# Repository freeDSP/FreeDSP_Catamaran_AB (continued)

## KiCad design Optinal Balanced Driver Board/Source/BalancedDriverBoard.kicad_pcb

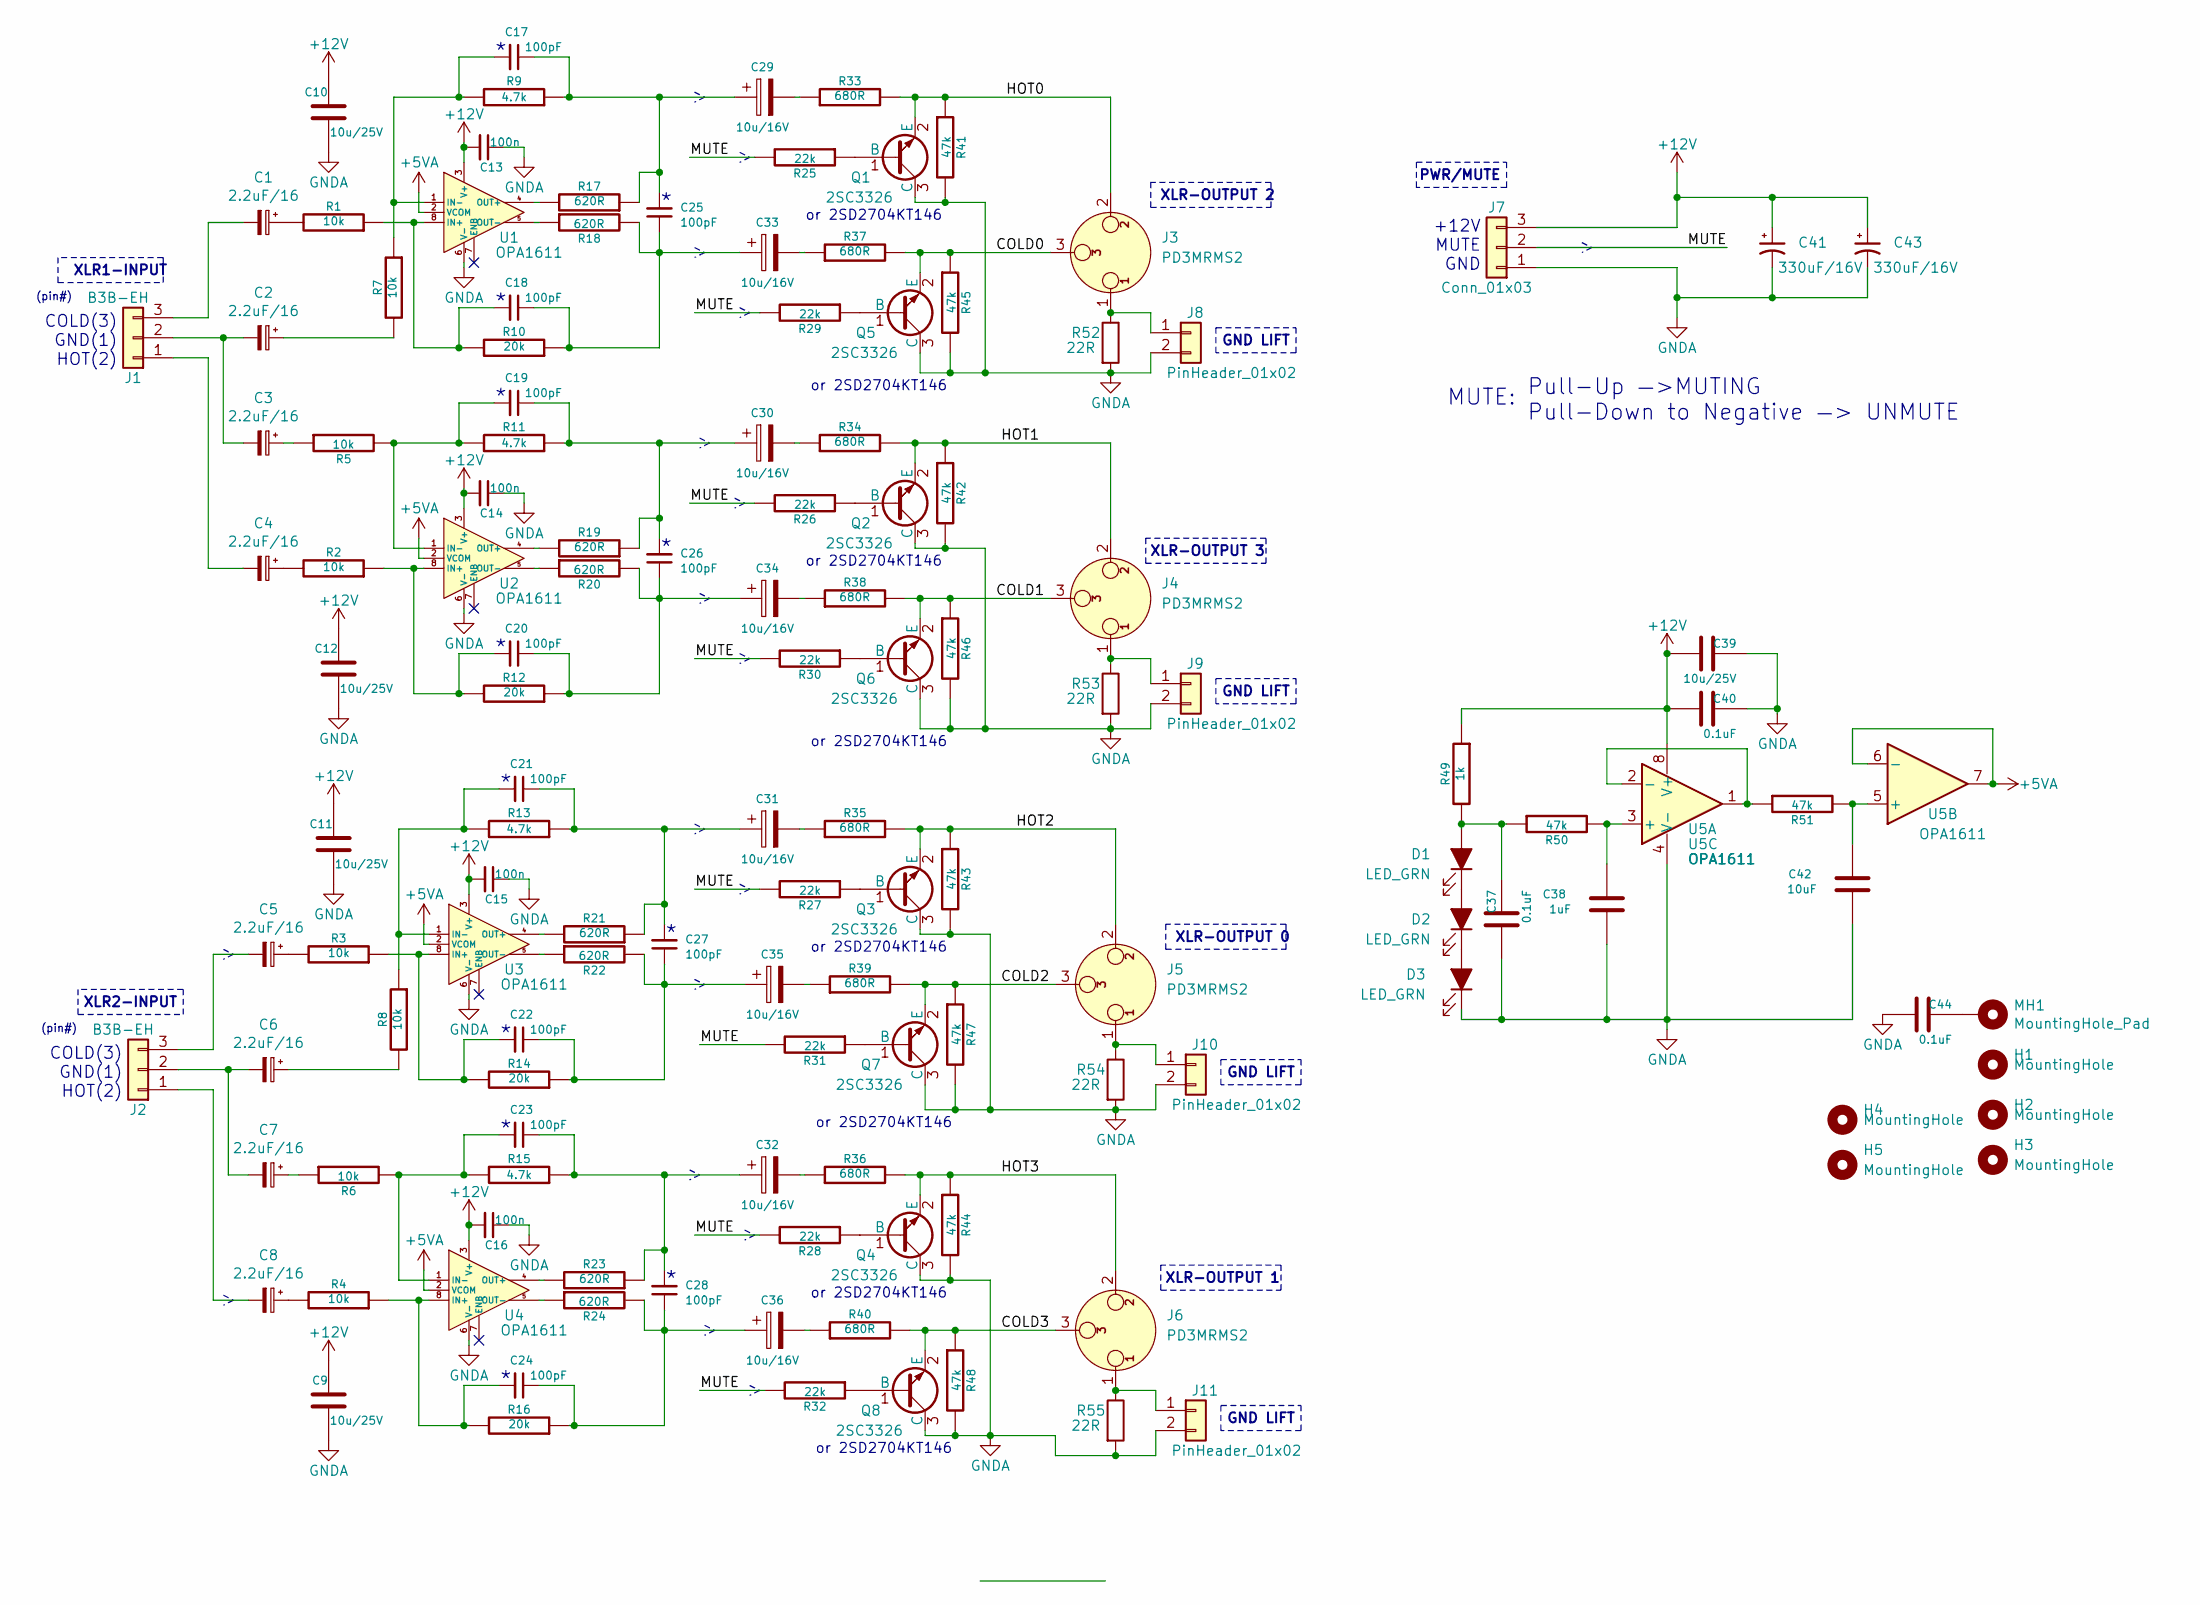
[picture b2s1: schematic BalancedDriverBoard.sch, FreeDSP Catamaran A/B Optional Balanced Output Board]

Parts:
C1, C2, C3, C4, C5, C6, C7, C8: 2.2uF/16; CP_Combo_D5.0mm_P2-5mm
C9, C10, C11, C12, C39: 10u/25V; C_0805_HandSoldering
C13, C14, C15, C16: 100n; C_0805_HandSoldering
C17, C18, C19, C20, C21, C22, C23, C24, C25, C26, C27, C28: 100pF; C_0805_HandSoldering
C29, C30, C31, C32, C33, C34, C35, C36: 10u/16V; CP_Radial_D5.0mm_P2.00mm
C37, C40, C44: 0.1uF; C_0805_HandSoldering
C38: 1uF; C_0805_HandSoldering
C41, C43: 330uF/16V; CP_Radial_D10.0mm_P2.50mm_P5.00mm
C42: 10uF; C_0805_HandSoldering
D1, D2, D3: LED_GRN; LED_0603_HandSoldering
H1, H2, H3, H4, H5: MountingHole; MountingHole_3.2mm_M3_Pad
J1, J2: B3B-EH; JST_XH_B3B-XH-AM_1x03_P2.50mm_Vertical
J3, J4, J5, J6: PD3MRMS2; SWITCHCRAFT_PD3MRMS2
J7: Conn_01x03; PinHeader_1x03_P2.54mm_Vertical
J8, J9, J10, J11: PinHeader_01x02; PinHeader_1x02_P2.54mm_Vertical
MH1: MountingHole_Pad; MountingHole_3.2mm_M3_Pad_Via
Q1, Q2, Q3, Q4, Q5, Q6, Q7, Q8: 2SC3326; SOT-23
R1, R2, R3, R4, R5, R6, R7, R8: 10k; R_0805_HandSoldering
R9, R11, R13, R15: 4.7k; R_0805_HandSoldering
R10, R12, R14, R16: 20k; R_0805_HandSoldering
R17, R18, R19, R20, R21, R22, R23, R24: 620R; R_0805_HandSoldering
R25, R26, R27, R28, R29, R30, R31, R32: 22k; R_0805_HandSoldering
R33, R34, R35, R36, R37, R38, R39, R40: 680R; R_0805_HandSoldering
R41, R42, R43, R44, R45, R46, R47, R48, R50, R51: 47k; R_0805_HandSoldering
R49: 1k; R_0805_HandSoldering
R52, R53, R54, R55: 22R; R_0805_HandSoldering
U1, U2, U3, U4, U5: OPA1611; SOIC-8_3.9x4.9mm_P1.27mm

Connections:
+5VA: U1.2 (VCOM), U2.2 (VCOM), U3.2 (VCOM), U4.2 (VCOM), U5.6 (-), U5.7
+12V: C9.1, C10.1, C11.1, C12.1, C13.2, C14.2, C15.2, C16.2, C39.1, C40.1, C41.1, C43.1, J7.3, R49.1, U1.3 (V+), U2.3 (V+), U3.3 (V+), U4.3 (V+), U5.8 (V+)
/COLD0: J3.3, Q5.2 (E), R37.2, R45.1
/COLD1: J4.3, Q6.2 (E), R38.2, R46.1
/COLD2: J5.3, Q7.2 (E), R39.2, R47.1
/COLD3: J6.3, Q8.2 (E), R40.2, R48.1
/HOT0: J3.2, Q1.2 (E), R33.2, R41.1
/HOT1: J4.2, Q2.2 (E), R34.2, R42.1
/HOT2: J5.2, Q3.2 (E), R35.2, R43.1
/HOT3: J6.2, Q4.2 (E), R36.2, R44.1
/MUTE: J7.2, R25.2, R26.2, R27.2, R28.2, R29.2, R30.2, R31.2, R32.2
GNDA: C9.2, C10.2, C11.2, C12.2, C13.1, C14.1, C15.1, C16.1, C37.1, C38.2, C39.2, C40.2, C41.2, C42.2, C43.2, C44.1, D3.1 (K), J7.1, J8.2, J9.2, J10.2, J11.2, Q1.3 (C), Q2.3 (C), Q3.3 (C), Q4.3 (C), Q5.3 (C), Q6.3 (C), Q7.3 (C), Q8.3 (C), R41.2, R42.2, R43.2, R44.2, R45.2, R46.2, R47.2, R48.2, R52.2, R53.2, R54.2, R55.2, U1.6 (V-), U2.6 (V-), U3.6 (V-), U4.6 (V-), U5.4 (V-)
unnamed: C1.1, R1.2
unnamed: C1.2, J1.3
unnamed: C2.1, R7.2
unnamed: C2.2, C3.2, J1.2
unnamed: C3.1, R5.1
unnamed: C4.1, R2.2
unnamed: C4.2, J1.1
unnamed: C5.1, R3.2
unnamed: C5.2, J2.3
unnamed: C6.1, R8.2
unnamed: C6.2, C7.2, J2.2
unnamed: C7.1, R6.1
unnamed: C8.1, R4.2
unnamed: C8.2, J2.1
unnamed: C17.1, C25.2, C29.1, R9.1, R17.1
unnamed: C17.2, R7.1, R9.2, U1.1 (IN-)
unnamed: C18.1, C25.1, C33.1, R10.1, R18.2
unnamed: C18.2, R1.1, R10.2, U1.8 (IN+)
unnamed: C19.1, C26.2, C30.1, R11.1, R19.1
unnamed: C19.2, R5.2, R11.2, U2.1 (IN-)
unnamed: C20.1, C26.1, C34.1, R12.1, R20.2
unnamed: C20.2, R2.1, R12.2, U2.8 (IN+)
unnamed: C21.1, C27.2, C31.1, R13.1, R21.1
unnamed: C21.2, R8.1, R13.2, U3.1 (IN-)
unnamed: C22.1, C27.1, C35.1, R14.1, R22.2
unnamed: C22.2, R3.1, R14.2, U3.8 (IN+)
unnamed: C23.1, C28.2, C32.1, R15.1, R23.1
unnamed: C23.2, R6.2, R15.2, U4.1 (IN-)
unnamed: C24.1, C28.1, C36.1, R16.1, R24.2
unnamed: C24.2, R4.1, R16.2, U4.8 (IN+)
unnamed: C29.2, R33.1
unnamed: C30.2, R34.1
unnamed: C31.2, R35.1
unnamed: C32.2, R36.1
unnamed: C33.2, R37.1
unnamed: C34.2, R38.1
unnamed: C35.2, R39.1
unnamed: C36.2, R40.1
unnamed: C37.2, D1.2 (A), R49.2, R50.1
unnamed: C38.1, R50.2, U5.3 (+)
unnamed: C42.1, R51.2, U5.5 (+)
unnamed: C44.2, MH1.1
unnamed: D1.1 (K), D2.2 (A)
unnamed: D2.1 (K), D3.2 (A)
unnamed: J3.1, J8.1, R52.1
unnamed: J4.1, J9.1, R53.1
unnamed: J5.1, J10.1, R54.1
unnamed: J6.1, J11.1, R55.1
unnamed: Q1.1 (B), R25.1
unnamed: Q2.1 (B), R26.1
unnamed: Q3.1 (B), R27.1
unnamed: Q4.1 (B), R28.1
unnamed: Q5.1 (B), R29.1
unnamed: Q6.1 (B), R30.1
unnamed: Q7.1 (B), R31.1
unnamed: Q8.1 (B), R32.1
unnamed: R17.2, U1.4 (OUT+)
unnamed: R18.1, U1.5 (OUT-)
unnamed: R19.2, U2.4 (OUT+)
unnamed: R20.1, U2.5 (OUT-)
unnamed: R21.2, U3.4 (OUT+)
unnamed: R22.1, U3.5 (OUT-)
unnamed: R23.2, U4.4 (OUT+)
unnamed: R24.1, U4.5 (OUT-)
unnamed: R51.1, U5.1, U5.2 (-)

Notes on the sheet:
XLR1-INPUT
(pin#)
COLD(3) GND(1) HOT(2)
PWR/MUTE
or 2SD2704KT146
XLR2-INPUT
+12V MUTE GND
Pull-Up —>MUTING Pull-Down to Negative —> UNMUTE
MUTE:
XLR-OUTPUT 0
XLR-OUTPUT 1
XLR-OUTPUT 2
XLR-OUTPUT 3
GND LIFT

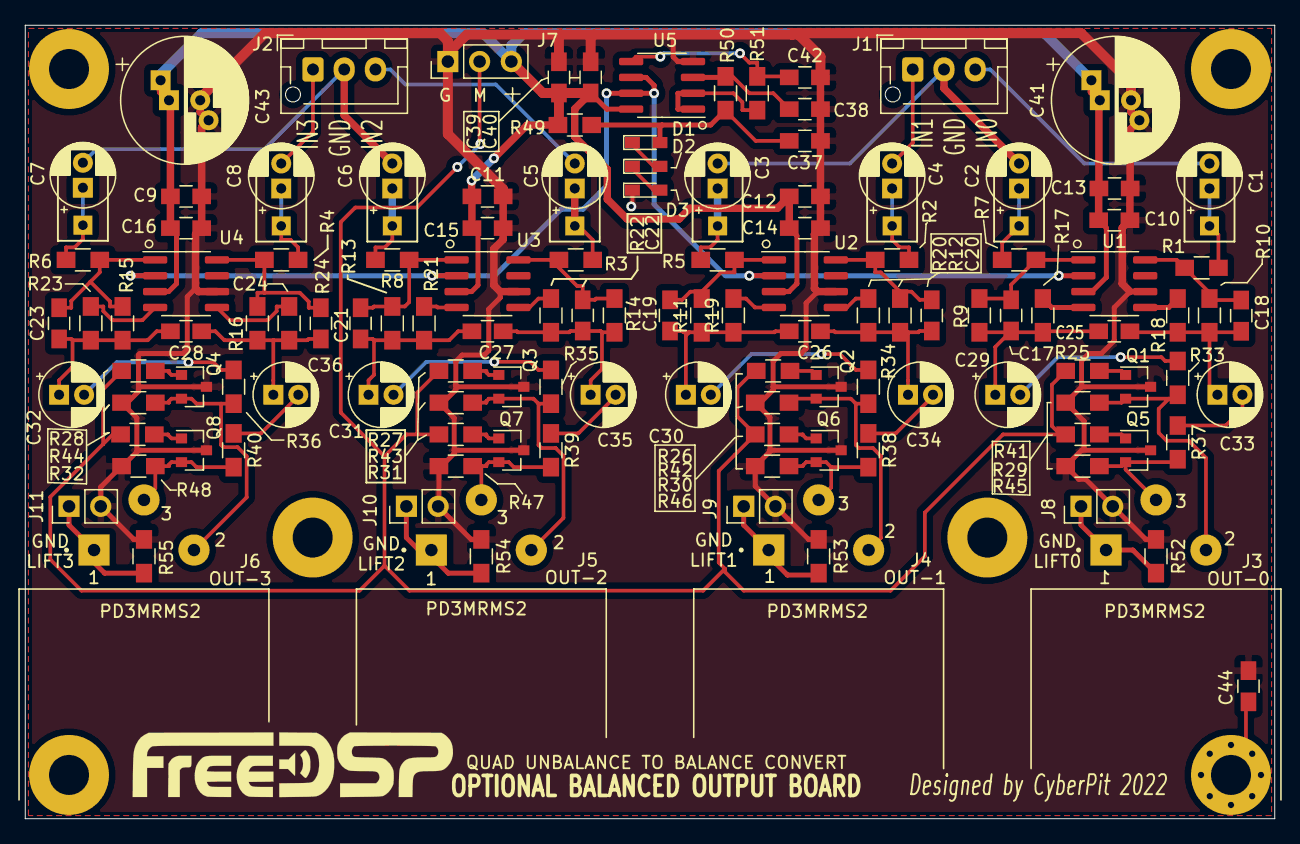
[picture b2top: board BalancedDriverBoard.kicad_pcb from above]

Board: 2 copper layers, 100.0 x 63.5 mm, 132 parts (0 on the bottom side), 77 nets.

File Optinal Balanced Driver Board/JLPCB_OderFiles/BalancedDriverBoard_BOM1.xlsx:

Comment | Designator | Footprint | JLCPCB Part #（optional）
OPA1611 | U1 | Package_SO:SOIC-8_3.9x4.9mm_P1.27mm | C86723
OPA1611 | U2 | Package_SO:SOIC-8_3.9x4.9mm_P1.27mm | C86723
OPA1611 | U3 | Package_SO:SOIC-8_3.9x4.9mm_P1.27mm | C86723
OPA1611 | U4 | Package_SO:SOIC-8_3.9x4.9mm_P1.27mm | C86723
OPA1611 | U5 | Package_SO:SOIC-8_3.9x4.9mm_P1.27mm | C86723
2SC3326 | Q1 | TO_SOT_Packages_SMD:SOT-23 | C79973
2SC3326 | Q2 | TO_SOT_Packages_SMD:SOT-23 | C79973
2SC3326 | Q3 | TO_SOT_Packages_SMD:SOT-23 | C79973
2SC3326 | Q4 | TO_SOT_Packages_SMD:SOT-23 | C79973
2SC3326 | Q5 | TO_SOT_Packages_SMD:SOT-23 | C79973
2SC3326 | Q6 | TO_SOT_Packages_SMD:SOT-23 | C79973
2SC3326 | Q7 | TO_SOT_Packages_SMD:SOT-23 | C79973
2SC3326 | Q8 | TO_SOT_Packages_SMD:SOT-23 | C79973
100n | C13 | Capacitors_SMD:C_0805_HandSoldering | C49678
100n | C14 | Capacitors_SMD:C_0805_HandSoldering | C49678
100n | C15 | Capacitors_SMD:C_0805_HandSoldering | C49678
100n | C16 | Capacitors_SMD:C_0805_HandSoldering | C49678
0.1uF | C37 | Capacitors_SMD:C_0805_HandSoldering | C49678
0.1uF | C40 | Capacitors_SMD:C_0805_HandSoldering | C49678
0.1uF | C44 | Capacitors_SMD:C_0805_HandSoldering | C49678
20k | R10 | Resistors_SMD:R_0805_HandSoldering | C4328
20k | R12 | Resistors_SMD:R_0805_HandSoldering | C4328
20k | R14 | Resistors_SMD:R_0805_HandSoldering | C4328
20k | R16 | Resistors_SMD:R_0805_HandSoldering | C4328
1uF | C38 | Capacitors_SMD:C_0805_HandSoldering | C28323
LED_RED | D1 | LEDs:LED_0603_HandSoldering | C2286
LED_RED | D2 | LEDs:LED_0603_HandSoldering | C2286
LED_RED | D3 | LEDs:LED_0603_HandSoldering | C2286
100pF | C17 | Capacitors_SMD:C_0805_HandSoldering | C1790
100pF | C18 | Capacitors_SMD:C_0805_HandSoldering | C1790
100pF | C19 | Capacitors_SMD:C_0805_HandSoldering | C1790
100pF | C20 | Capacitors_SMD:C_0805_HandSoldering | C1790
100pF | C21 | Capacitors_SMD:C_0805_HandSoldering | C1790
100pF | C22 | Capacitors_SMD:C_0805_HandSoldering | C1790
100pF | C23 | Capacitors_SMD:C_0805_HandSoldering | C1790
100pF | C24 | Capacitors_SMD:C_0805_HandSoldering | C1790
100pF | C25 | Capacitors_SMD:C_0805_HandSoldering | C1790
100pF | C26 | Capacitors_SMD:C_0805_HandSoldering | C1790
100pF | C27 | Capacitors_SMD:C_0805_HandSoldering | C1790
100pF | C28 | Capacitors_SMD:C_0805_HandSoldering | C1790
680R | R33 | Resistors_SMD:R_0805_HandSoldering | C17798
680R | R34 | Resistors_SMD:R_0805_HandSoldering | C17798
680R | R35 | Resistors_SMD:R_0805_HandSoldering | C17798
680R | R36 | Resistors_SMD:R_0805_HandSoldering | C17798
680R | R37 | Resistors_SMD:R_0805_HandSoldering | C17798
680R | R38 | Resistors_SMD:R_0805_HandSoldering | C17798
680R | R39 | Resistors_SMD:R_0805_HandSoldering | C17798
680R | R40 | Resistors_SMD:R_0805_HandSoldering | C17798
620R | R17 | Resistors_SMD:R_0805_HandSoldering | C17782
620R | R18 | Resistors_SMD:R_0805_HandSoldering | C17782
620R | R19 | Resistors_SMD:R_0805_HandSoldering | C17782
620R | R20 | Resistors_SMD:R_0805_HandSoldering | C17782
620R | R21 | Resistors_SMD:R_0805_HandSoldering | C17782
620R | R22 | Resistors_SMD:R_0805_HandSoldering | C17782
620R | R23 | Resistors_SMD:R_0805_HandSoldering | C17782
620R | R24 | Resistors_SMD:R_0805_HandSoldering | C17782
47k | R41 | Resistors_SMD:R_0805_HandSoldering | C17713
47k | R42 | Resistors_SMD:R_0805_HandSoldering | C17713
47k | R43 | Resistors_SMD:R_0805_HandSoldering | C17713
47k | R44 | Resistors_SMD:R_0805_HandSoldering | C17713
47k | R45 | Resistors_SMD:R_0805_HandSoldering | C17713
47k | R46 | Resistors_SMD:R_0805_HandSoldering | C17713
47k | R47 | Resistors_SMD:R_0805_HandSoldering | C17713
47k | R48 | Resistors_SMD:R_0805_HandSoldering | C17713
47k | R50 | Resistors_SMD:R_0805_HandSoldering | C17713
47k | R51 | Resistors_SMD:R_0805_HandSoldering | C17713
4.7k | R9 | Resistors_SMD:R_0805_HandSoldering | C17673
4.7k | R11 | Resistors_SMD:R_0805_HandSoldering | C17673
4.7k | R13 | Resistors_SMD:R_0805_HandSoldering | C17673
4.7k | R15 | Resistors_SMD:R_0805_HandSoldering | C17673
22R | R52 | Resistors_SMD:R_0805_HandSoldering | C17561
22R | R53 | Resistors_SMD:R_0805_HandSoldering | C17561
22R | R54 | Resistors_SMD:R_0805_HandSoldering | C17561
22R | R55 | Resistors_SMD:R_0805_HandSoldering | C17561
22k | R25 | Resistors_SMD:R_0805_HandSoldering | C17560
22k | R26 | Resistors_SMD:R_0805_HandSoldering | C17560
22k | R27 | Resistors_SMD:R_0805_HandSoldering | C17560
22k | R28 | Resistors_SMD:R_0805_HandSoldering | C17560
22k | R29 | Resistors_SMD:R_0805_HandSoldering | C17560
22k | R30 | Resistors_SMD:R_0805_HandSoldering | C17560
22k | R31 | Resistors_SMD:R_0805_HandSoldering | C17560
22k | R32 | Resistors_SMD:R_0805_HandSoldering | C17560
1k | R49 | Resistors_SMD:R_0805_HandSoldering | C17513
10k | R1 | Resistors_SMD:R_0805_HandSoldering | C17414
10k | R2 | Resistors_SMD:R_0805_HandSoldering | C17414
10k | R3 | Resistors_SMD:R_0805_HandSoldering | C17414
10k | R4 | Resistors_SMD:R_0805_HandSoldering | C17414
10k | R5 | Resistors_SMD:R_0805_HandSoldering | C17414
10k | R6 | Resistors_SMD:R_0805_HandSoldering | C17414
10k | R7 | Resistors_SMD:R_0805_HandSoldering | C17414
10k | R8 | Resistors_SMD:R_0805_HandSoldering | C17414
10u/25V | C9 | Capacitors_SMD:C_0805_HandSoldering | C15850
10u/25V | C10 | Capacitors_SMD:C_0805_HandSoldering | C15850
10u/25V | C11 | Capacitors_SMD:C_0805_HandSoldering | C15850
10u/25V | C12 | Capacitors_SMD:C_0805_HandSoldering | C15850
10u/25V | C39 | Capacitors_SMD:C_0805_HandSoldering | C15850
10uF | C42 | Capacitors_SMD:C_0805_HandSoldering | C15850
2.2uF/16 | C1 | Myfootprints:CP_Combo_D5.0mm_P2-5mm
2.2uF/16 | C2 | Myfootprints:CP_Combo_D5.0mm_P2-5mm
2.2uF/16 | C3 | Myfootprints:CP_Combo_D5.0mm_P2-5mm
2.2uF/16 | C4 | Myfootprints:CP_Combo_D5.0mm_P2-5mm
2.2uF/16 | C5 | Myfootprints:CP_Combo_D5.0mm_P2-5mm
2.2uF/16 | C6 | Myfootprints:CP_Combo_D5.0mm_P2-5mm
2.2uF/16 | C7 | Myfootprints:CP_Combo_D5.0mm_P2-5mm
2.2uF/16 | C8 | Myfootprints:CP_Combo_D5.0mm_P2-5mm
10u/16V | C29 | Capacitor_THT:CP_Radial_D5.0mm_P2.00mm
10u/16V | C30 | Capacitor_THT:CP_Radial_D5.0mm_P2.00mm
10u/16V | C31 | Capacitor_THT:CP_Radial_D5.0mm_P2.00mm
10u/16V | C32 | Capacitor_THT:CP_Radial_D5.0mm_P2.00mm
10u/16V | C33 | Capacitor_THT:CP_Radial_D5.0mm_P2.00mm
10u/16V | C34 | Capacitor_THT:CP_Radial_D5.0mm_P2.00mm
10u/16V | C35 | Capacitor_THT:CP_Radial_D5.0mm_P2.00mm
10u/16V | C36 | Capacitor_THT:CP_Radial_D5.0mm_P2.00mm
330uF/16V | C41 | Capacitor_THT:CP_Radial_D10.0mm_P2.50mm_P5.00mm
330uF/16V | C43 | Capacitor_THT:CP_Radial_D10.0mm_P2.50mm_P5.00mm
B3B-EH | J1 | Connector_JST:JST_XH_B3B-XH-AM_1x03_P2.50mm_Vertical
B3B-EH | J2 | Connector_JST:JST_XH_B3B-XH-AM_1x03_P2.50mm_Vertical
PD3MRMS2 | J3 | Myfootprints:SWITCHCRAFT_PD3MRMS2
PD3MRMS2 | J4 | Myfootprints:SWITCHCRAFT_PD3MRMS2
PD3MRMS2 | J5 | Myfootprints:SWITCHCRAFT_PD3MRMS2
PD3MRMS2 | J6 | Myfootprints:SWITCHCRAFT_PD3MRMS2
Conn_01x03 | J7 | Connector_PinHeader_2.54mm:PinHeader_1x03_P2.54mm_Vertical
PinHeader_01x02 | J8 | Connector_PinHeader_2.54mm:PinHeader_1x02_P2.54mm_Vertical
PinHeader_01x02 | J9 | Connector_PinHeader_2.54mm:PinHeader_1x02_P2.54mm_Vertical
PinHeader_01x02 | J10 | Connector_PinHeader_2.54mm:PinHeader_1x02_P2.54mm_Vertical
PinHeader_01x02 | J11 | Connector_PinHeader_2.54mm:PinHeader_1x02_P2.54mm_Vertical

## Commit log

2022-01-16 Image SnapShots
2022-01-16 FreeDSP Catamaran A/B Main Board
2022-01-16 Optional XLR Balanced Output Board
    4 unbalanced (Differential) inputs convert to Balanced XLR output.
    This is an optional board. Only for XLR connection.
    FreeDSP Catamaran has Differential Input and Output circuit, so basically this board is not necessary except for connecting XLR Cable.
2022-01-16 FreeDSP Catamaran Main Board
2022-01-16 Optional XLR Balaned Output Board
    ki-CAD Design Files
2022-01-16 A stereo construction image (Interlinked)
    A stereo construction image of FreeDSP Catamaran A/B
2022-01-16 Inital Design Released but not built yet.
    Not evaluated yet.
    Order at your own risk!
2022-01-19 JLPCB PCBA order required Files
2022-01-21 FreeDSP Catamaran A/B MainBoard diemension Drawing
2022-01-23 Add link to project page. (Japanese)
    This Product is under evaluation.
2022-01-24 Fixed wrong parts number U1 - U4 as C86715
2022-01-24 FIxed wong parts number U1 - U4 as C86715
2022-01-24 Fixed wrong parts number U1 - U4 as C86715.
2022-01-24 Fixed U1 - U4 parts number as OPA1632.
2022-01-24 Wrong Parts number U1 - U4
2022-02-12 Update Stacked Board Image drawing
2022-04-29 Version 0.21 JLPCB ordered Files
2022-04-29 FreeDSP Catamaran A/B version 0.21
    Changed minor silkscreen layouts
2022-04-29 FreeDSP Catamaran A/B Board version 0.21 Diemesions Drawing
2022-04-29 FreeDSP Catamaran A/B DSP Board Mechanical Drawing
2022-04-29 FreeDSP Catamaran A/B 0v21 Schematic
2022-04-29 FreeDSP Catamaran 0v21 Gerber Files
2022-04-29 FreeDSP Catamaran 0v21 SMD Placement File
2022-05-12 SMT had done. Start the evaluation....
2022-05-12 FreeDSP Catamaran A/B ver. 0.21 SMT by JLPCB
2022-05-17 Evaluated Schematic Crcuit Diagram.
2022-05-17 Evaluated SMT BOM List for JLPCB
2022-05-17 SMT Parts Placement File for 0v22 board.
2022-05-17 JLPC oder format Gerber/Drill Data and SMT BOM/CPL
2022-05-17 Version1.0 Gerber and SMT Data files for JLPCB
2022-05-17 Version 1.0 Release Ki-CAD Data Files
2022-05-17 FreeDSP Catamaran version 1.0 Released May. 18th, 2022
2022-05-17 Version 1.0 Released Schematic Circuit Diagram
2022-05-17 Version 0.21 Evaluated Stereo Linked Board Photo
2022-05-19 Version 1.0 Board 3D Rendering
2022-05-21 Version 0.21 Parts Mounted Board Photo
2022-05-21 TDM-LINK CABLE Photo
2022-05-29 Version0.21 Board Measured Audio Performances
2022-05-29 version 0.21 Board THD Campion Data (96kHz)
2022-05-29 Comparison THD Differential vs SingleEnd
2022-06-13 Some ADC gain resistors are trimmed.
    Resistor value changed. (R29, R34, R36, R46) for gain adjustment.
    The input and output reference level will be 2V RMS.
2022-06-13 Resistors value changed to trim the ADC gain
    Adjust the ADC part gain setting for 2V RMS I/O reference.
2022-06-13 Version 1.01 schematic Circuit Diagram and App
    Input gain adjusted (2V RMS) schematic and 4way channel divider application DSP Schematic.
2022-06-13 4way crossover Application and TDM-LINK function Test File.
    Master -> Set the jumper pin at the J11- "INT" position.
    Slave -> Set the jumper pin at the J11- "EXT" position.
    You can execute 512 steps of DSP codes @96kHz sampling.
2022-06-13 Measured Frequency Response (4way Channel Divider)
2022-07-09 PCBA order fromat files for JLPCB
    Version 1.2 Board Order format Gerber, Drill, Parts, Placement dat files.
2022-07-09 1v2 add auto-reboot feature on PGM-SW transnsition
    The reset switch was removed due to the automatic DSP reboot feature on the transition of the A/B program change.
2022-07-09 Version 1.2 board rederings
    Add a feature of the automatic reboot on the transition of A/B program select switch. The RESET button was removed.
2022-07-09 1v2 add Auto-Reboot feature on PGM-SW transnsition
2022-07-09 Version 1.2 added a feature of DSP Auto-Reload
    Added a feature of automatic DSP code reloads on the transition of A/B program select switch.
    The RESET button was removed. (No longer needed)
2022-07-09 Version 1.2 added a feature of DSP Auto-Reload
2022-07-31 FreeDSP Catamaran ADAU1701 SigmaStudio Projects
    SigmaStudio ADAU1701 Project FiIes
2022-11-13 Update README.md
    Modified readme text.
